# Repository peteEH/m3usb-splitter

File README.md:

# m3usb-splitter

tesla model 3 usb splitter

 -- splits a single usb port into a data only port (low power) and a charging power port
 -- option to provide either D+/D- short or a dedicated charging identification chip
 
 -- multiple PCB "variants" included, depends on the flash drive or cables used to attach to the splitter.

Tesla includes charging cables that short D+/D- together - these docking cables when used, properly idenify the usb source as a charging adaptor (USB spec)

Typical use case:

--- Samsung T5 500GB SSD plugs into the data port
--- included tesla charging cable for docking plugs into the power only port

BOM (exact or similar PNs):
(minimal)

2x UE27AC54100  USB Type A Receptacle - Right Angle, Through Hole
1x UP2-AH-1-TH  USB Type A Plug - Right Angle, Through Hole
1x 10uF, 0805, 10V Capacitor
1x 0 Ohm, 0805 Resistor
1x PCB (i.e. JLC or similar - about $2)

(with dedicated charger chip - add these parts)
1x TPS2514A   Dedicated D+/D- charger ID chip
1x 10uF, 0805, 10V Capacitor

## LICENSE ##
Hardware License is Creative Commons - Attribution 3.0

Feel free to use these files to learn, explore electronics.

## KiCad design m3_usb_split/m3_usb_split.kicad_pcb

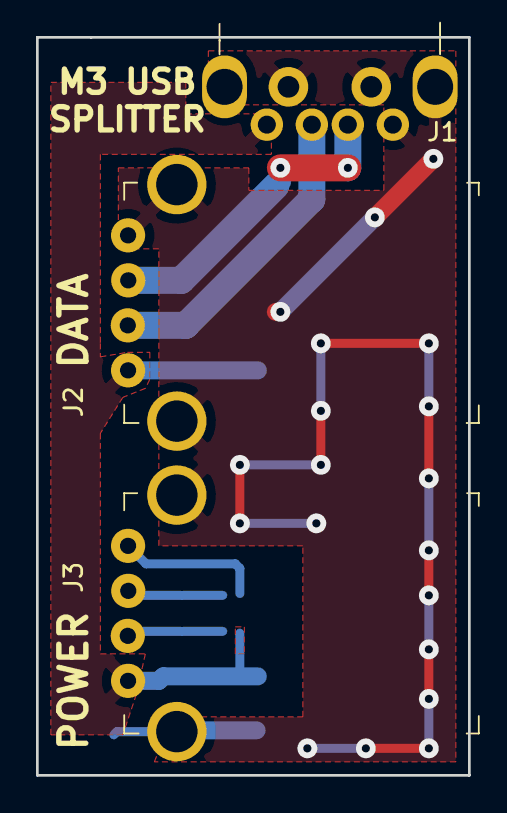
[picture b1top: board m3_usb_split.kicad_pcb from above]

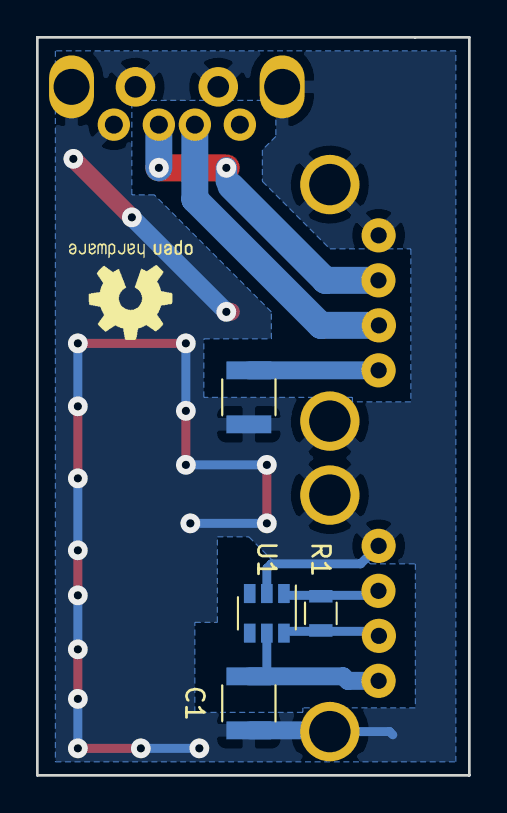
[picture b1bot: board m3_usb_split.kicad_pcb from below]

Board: 2 copper layers, 24.0 x 41.0 mm, 7 parts (4 on the bottom side), 6 nets.

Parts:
C1, C2: 10uF; C_1210
J1: UP2-AH-1-TH; USB_Male_A_UP2-AH-1-TH
J2, J3: UE27AC54100; USB_A_Female_UE27AC54100
R1: 0R; R_0805
U1: TPS2514A; SOT-23-6

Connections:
GND: C1.2, C2.2, J1.4, J1.5, J2.4, J2.5, J3.4, J3.5, U1.2
unnamed: J1.2, J2.2
unnamed: J1.3, J2.3
unnamed: J3.2, R1.2, U1.6
unnamed: J3.3, R1.1, U1.1
VBUS: C1.1, C2.1, J1.1, J2.1, J3.1, U1.5

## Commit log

2019-10-19 created readme file
    initial readme
2019-10-19 added kicad project directory files
2019-10-26 added license
2019-10-26 added BOM info
